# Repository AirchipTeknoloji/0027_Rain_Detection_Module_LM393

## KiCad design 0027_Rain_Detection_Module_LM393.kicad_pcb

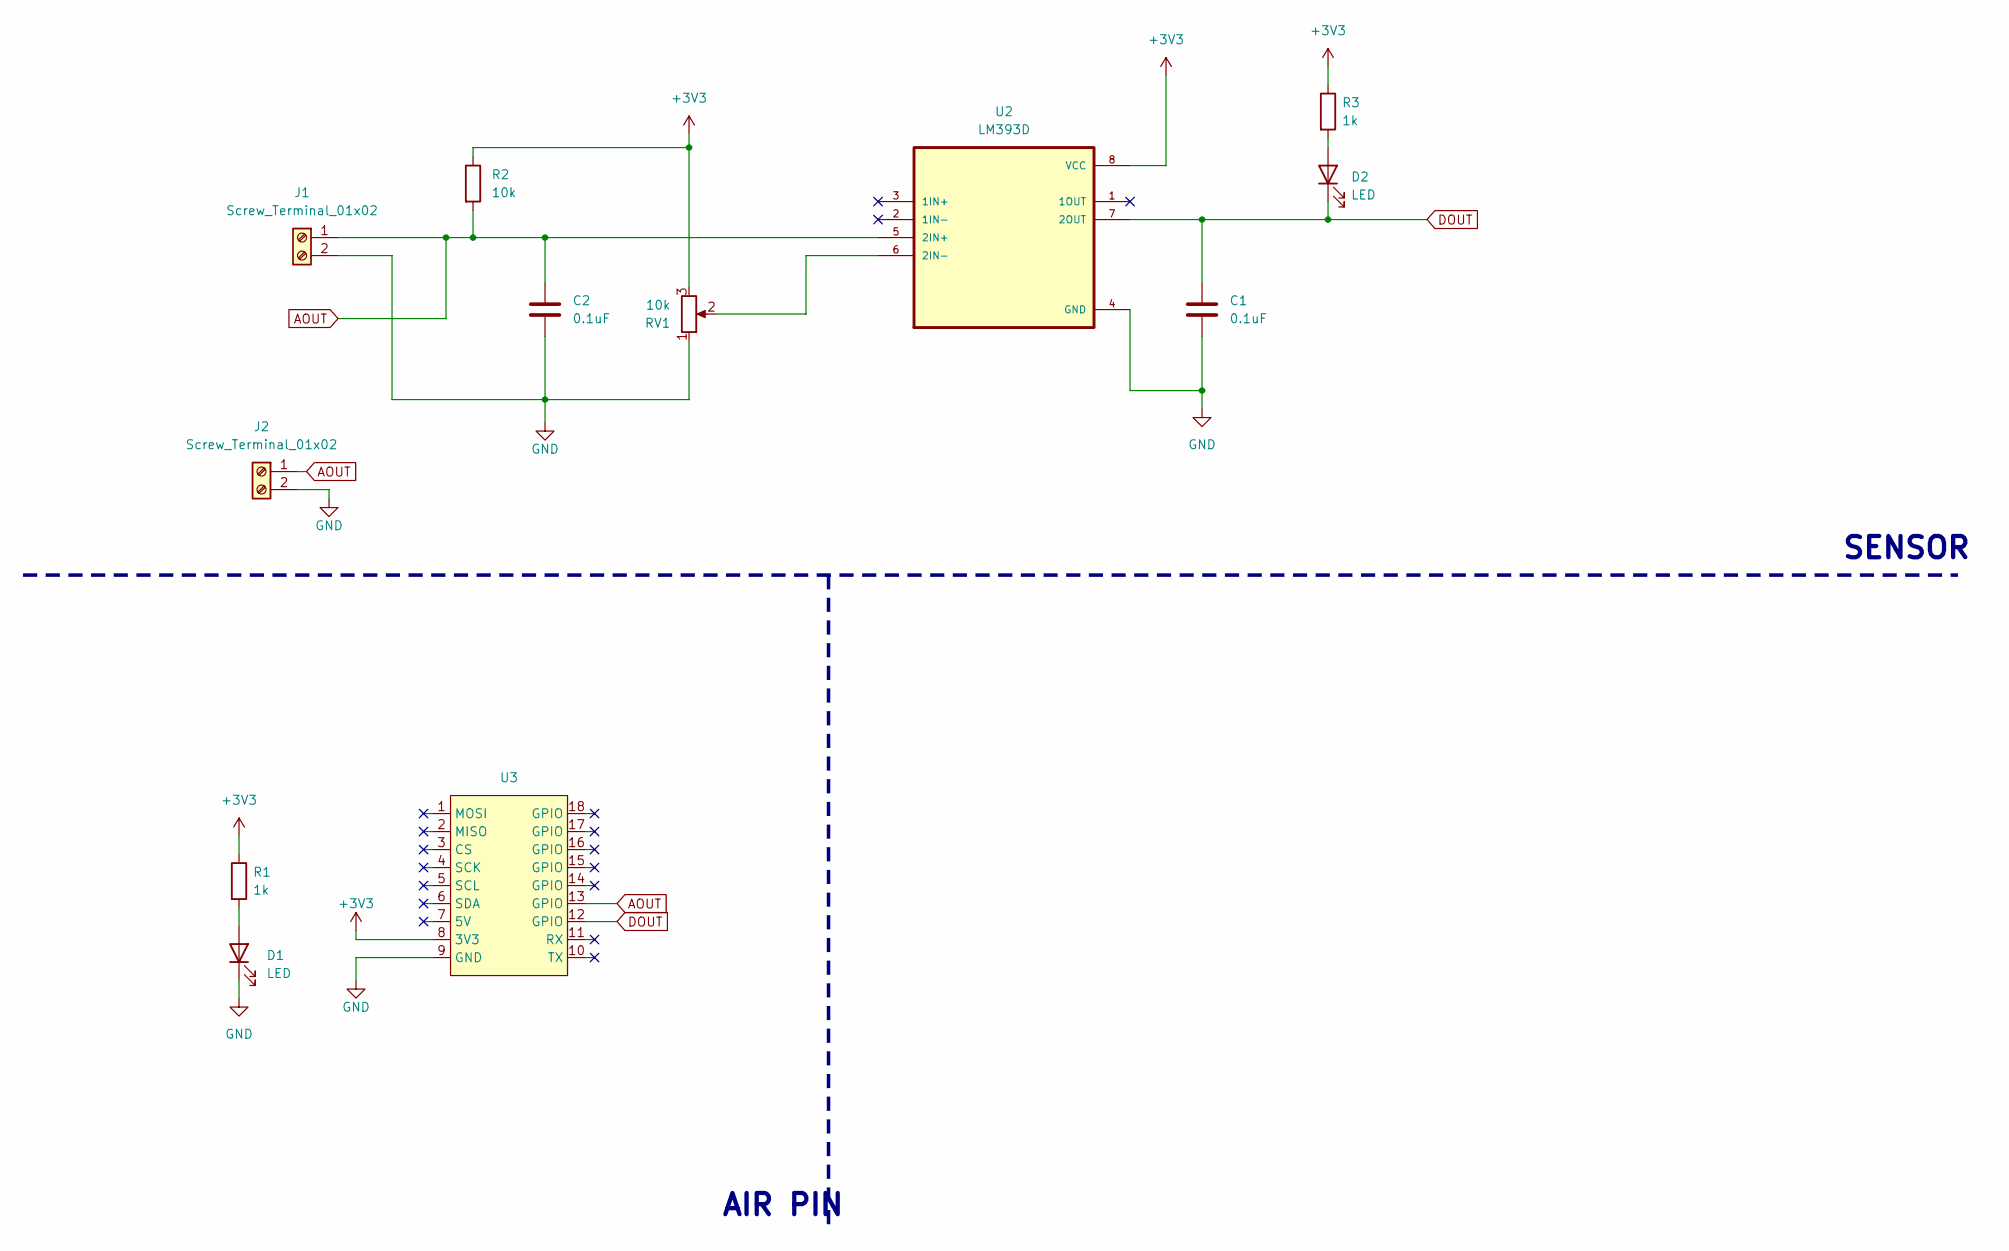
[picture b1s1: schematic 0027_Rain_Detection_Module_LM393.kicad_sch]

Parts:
C1, C2: 0.1uF; C_0805_2012Metric
D1, D2: LED; LED_0805_2012Metric
J1: Screw_Terminal_01x02; TerminalBlock_4Ucon_1x02_P3.50mm_Horizontal
J2: Screw_Terminal_01x02; rain
R1, R3: 1k; R_0805_2012Metric
R2: 10k; R_0805_2012Metric
RV1: 10k; 3362P_1
U2: LM393D; SOIC127P599X175-8N
U3: air_module

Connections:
+3V3: R1.1, R2.1, R3.1, RV1.3, U2.8 (VCC), U3.8 (3V3); also elsewhere on the board
AOUT: C2.1, J1.1, J2.1, R2.2, U2.5 (2IN+), U3.13 (GPIO)
DOUT: C1.1, D2.1 (K), U2.7 (2OUT), U3.12 (GPIO)
GND: C1.2, C2.2, D1.1 (K), J1.2, J2.2, RV1.1, U2.4 (GND), U3.9 (GND); also elsewhere on the board
unnamed: D1.2 (A), R1.2
unnamed: D2.2 (A), R3.2
unnamed 6: RV1.2, U2.6 (2IN-); also elsewhere on the board

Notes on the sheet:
SENSOR
AIR PIN

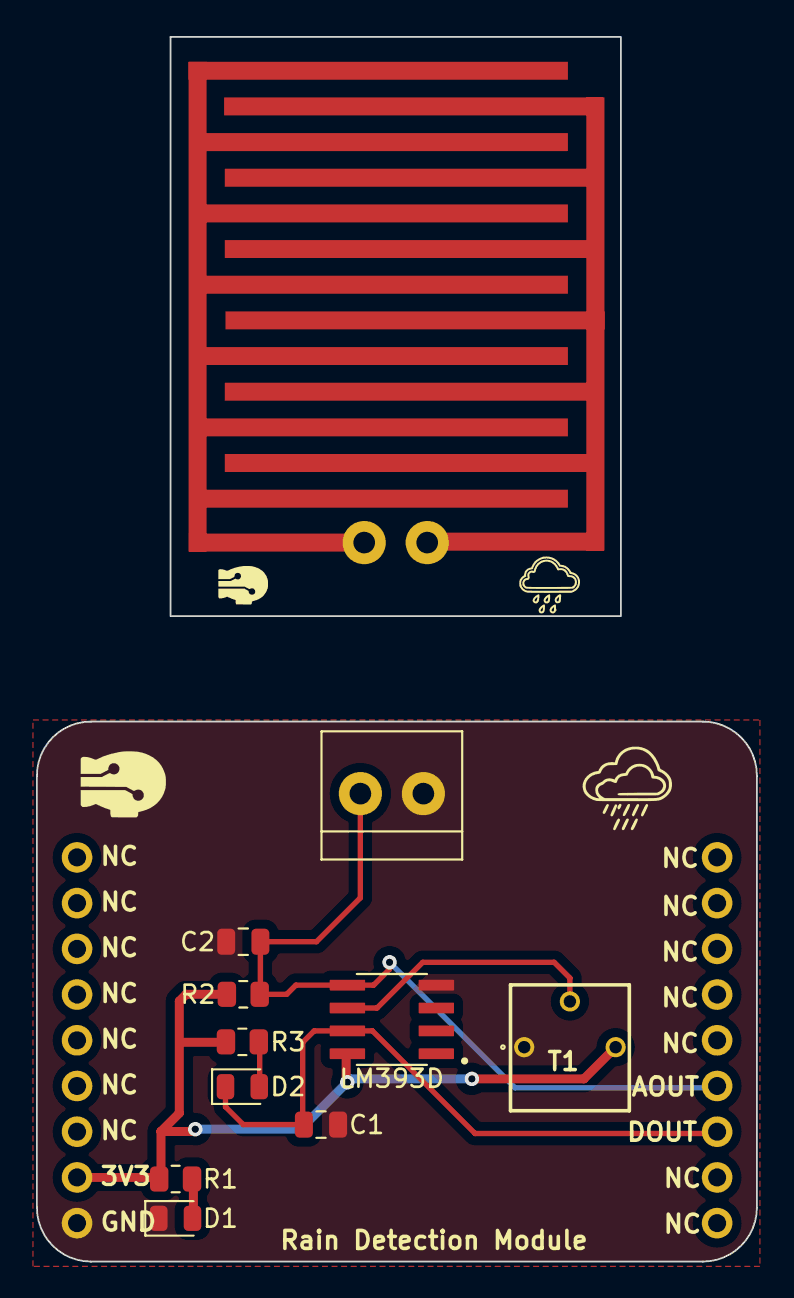
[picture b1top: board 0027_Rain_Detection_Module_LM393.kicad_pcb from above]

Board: 2 copper layers, 40.0 x 30.0 mm, 12 parts (0 on the bottom side), 7 nets.

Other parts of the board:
T1: 10k; 3362P_1

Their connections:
+3V3: T1.3; also elsewhere on the board
GND: T1.1; also elsewhere on the board
unnamed 6: T1.2; also elsewhere on the board
